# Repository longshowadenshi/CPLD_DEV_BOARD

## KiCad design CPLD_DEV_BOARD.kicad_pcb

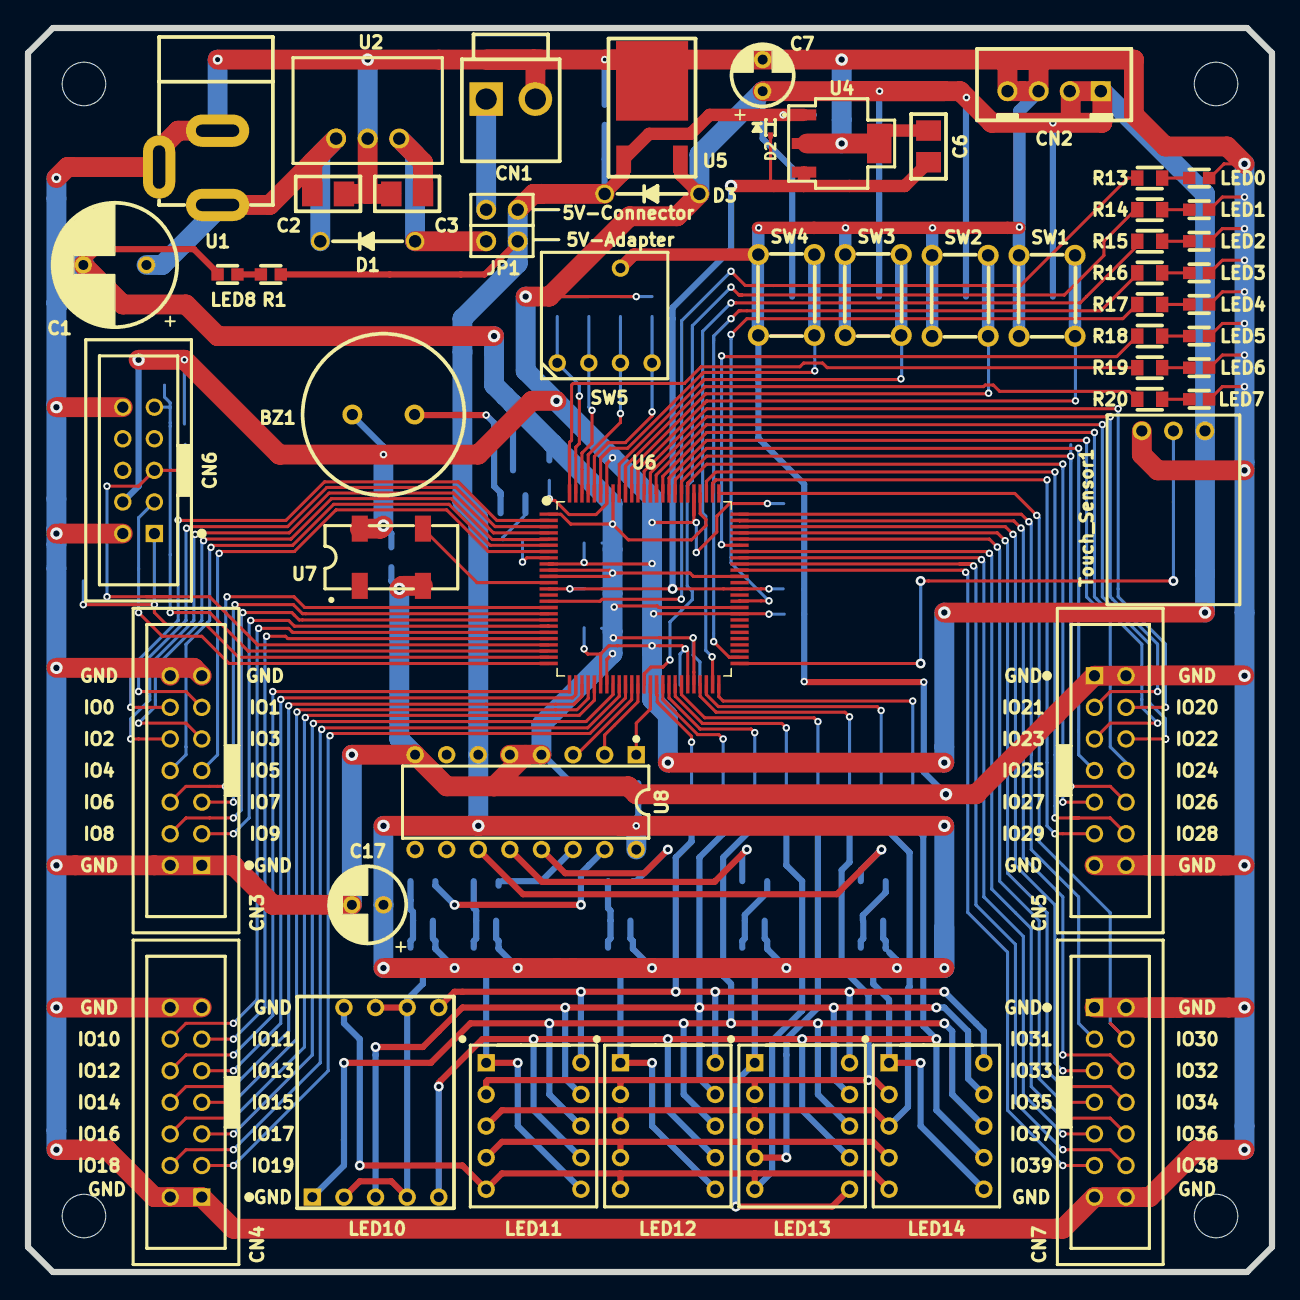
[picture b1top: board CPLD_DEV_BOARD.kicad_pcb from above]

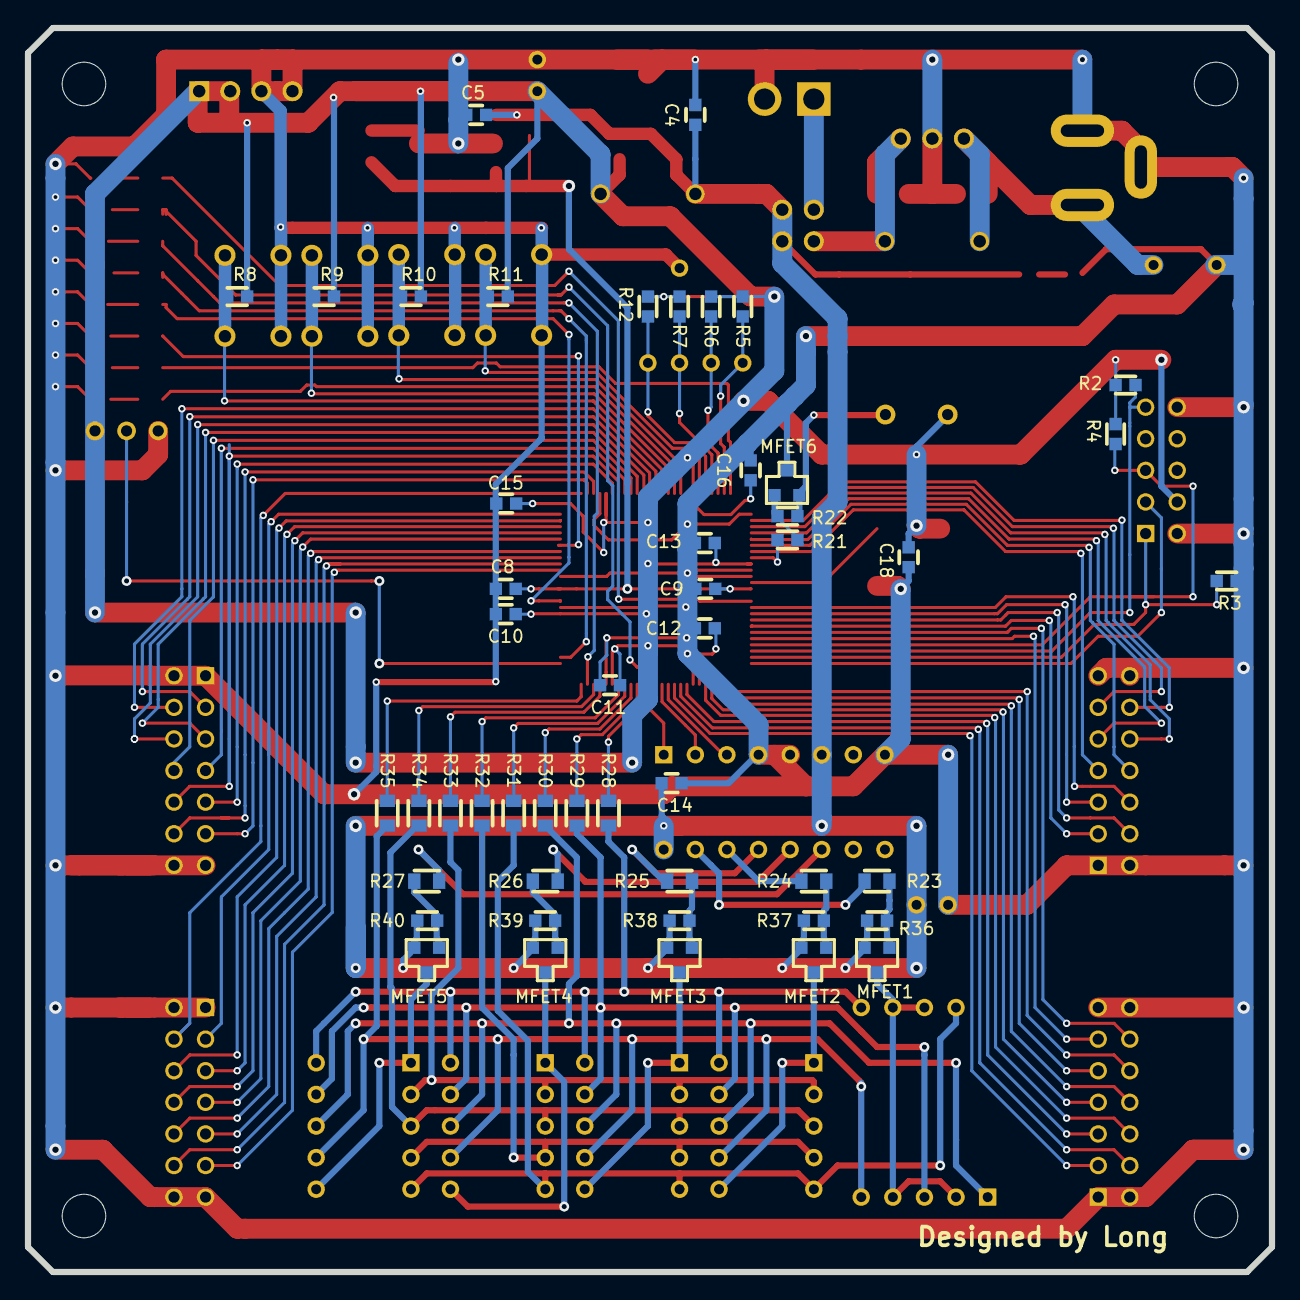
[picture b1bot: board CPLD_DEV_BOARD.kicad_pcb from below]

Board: 2 copper layers, 100.0 x 100.0 mm, 103 parts (49 on the bottom side), 115 nets.

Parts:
BZ1: Buzzer; BUZ_5_12.6
C1: 470uf/25V; 470uF-25V
C2, C3, C6: 10uF; C_3216
C4, C8, C9, C10, C11, C12, C13, C14, C15, C16, C18: 0.1uF; C0603C104Z3VACTU
C5: 1uF; C0603C104Z3VACTU
C7: 22uf/16V; 10uF-16v
C17: 220uF/16V; 220uF-16V
CN1: B2B-VH; cn_B2P-VH
CN2: B4B-XH-A; cn_B4B-XH-A
CN3, CN4, CN5, CN7: 14PIN; HIF3FC-14PA
CN6: HIF3FC-10A-2.54DSA; HIF3FC-10PA
D1, D3: 1DS4
D2: RB521S30T1G
JP1: jumper
LED0, LED1, LED2, LED3, LED4, LED5, LED6, LED7: BLUE; C1608C0G1H682J
LED8: GREEN; C1608C0G1H682J
LED10: LED__HDSP_5507; HDSP5307
LED11, LED12, LED13, LED14: SA39-12SRWA; SA39-129RWB
MFET1, MFET2, MFET3, MFET4, MFET5, MFET6: SSM3J334R
R1: 470; C1608C0G1H682J
R2, R3, R4: 4.7k; C1608C0G1H682J
R5, R6, R7, R8, R9, R10, R11, R12, R21, R22, R36, R37, R38, R39, R40: 10k; C1608C0G1H682J
R13, R14, R15, R16, R17, R18, R19, R20, R23, R24, R25, R26, R27, R28, R29, R30, R31, R32, R33, R34, R35: 1k; C_1220
SW1, SW2, SW3, SW4: SKHHBY
SW5: SW_Coded; S-2030A
Touch_Sensor1: 3PIN; Touch_Sensor
U1: MJ-179P; MJ179P
U2: R-78E5.0-0.5
U4: MCP1826S
U5: NJM2391DL1-33
U6: 5M80ZT100C5N
U7: SG636PCE8M
U8: 74HCT138; 74HC161AP

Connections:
+1V8: C6.1, C8.1, C9.1, D2.1, U4.3, U6.13, U6.63
+3V3: BZ1.1, C7.1, C10.1, C11.1, C12.1, C13.1, C15.1, C16.1, C18.1, CN2.1, CN2.2, CN6.4, D3.1, R2.1, R4.1, R5.1, R6.1, R7.1, R8.1, R9.1, R10.1, R11.1, R12.1, Touch_Sensor1.1, U5.3, U6.9, U6.31, U6.45, U6.59, U6.80, U6.94, U7.4
+5V: C4.1, C5.1, C14.1, C17.1, D2.2, D3.2, JP1.2, JP1.4, MFET1.2, MFET2.2, MFET3.2, MFET4.2, MFET5.2, R1.1, R36.2, R37.2, R38.2, R39.2, R40.2, U4.1, U5.1, U8.6, U8.16
/5M80ZT100C5N/Buzzer: R21.2, U6.8
/5M80ZT100C5N/COL0: U6.39, U8.1
/5M80ZT100C5N/COL1: U6.37, U8.2
/5M80ZT100C5N/COL2: U6.36, U8.3
/5M80ZT100C5N/IO0: CN3.12, U6.2
/5M80ZT100C5N/IO1: CN3.11, U6.3
/5M80ZT100C5N/IO2: CN3.10, U6.4
/5M80ZT100C5N/IO3: CN3.9, U6.5
/5M80ZT100C5N/IO4: CN3.8, U6.6
/5M80ZT100C5N/IO5: CN3.7, U6.7
/5M80ZT100C5N/IO6: CN3.6, U6.16
/5M80ZT100C5N/IO7: CN3.5, U6.17
/5M80ZT100C5N/IO8: CN3.4, U6.18
/5M80ZT100C5N/IO9: CN3.3, U6.19
/5M80ZT100C5N/IO10: CN4.12, U6.20
/5M80ZT100C5N/IO11: CN4.11, U6.21
/5M80ZT100C5N/IO12: CN4.10, U6.26
/5M80ZT100C5N/IO13: CN4.9, U6.27
/5M80ZT100C5N/IO14: CN4.8, U6.28
/5M80ZT100C5N/IO15: CN4.7, U6.29
/5M80ZT100C5N/IO16: CN4.6, U6.30
/5M80ZT100C5N/IO17: CN4.5, U6.33
/5M80ZT100C5N/IO18: CN4.4, U6.34
/5M80ZT100C5N/IO19: CN4.3, U6.35
/5M80ZT100C5N/IO20: CN5.4, U6.88
/5M80ZT100C5N/IO21: CN5.3, U6.87
/5M80ZT100C5N/IO22: CN5.6, U6.86
/5M80ZT100C5N/IO23: CN5.5, U6.85
/5M80ZT100C5N/IO24: CN5.8, U6.84
/5M80ZT100C5N/IO25: CN5.7, U6.83
/5M80ZT100C5N/IO26: CN5.10, U6.82
/5M80ZT100C5N/IO27: CN5.9, U6.81
/5M80ZT100C5N/IO28: CN5.12, U6.78
/5M80ZT100C5N/IO29: CN5.11, U6.77
/5M80ZT100C5N/IO30: CN7.4, U6.76
/5M80ZT100C5N/IO31: CN7.3, U6.75
/5M80ZT100C5N/IO32: CN7.6, U6.74
/5M80ZT100C5N/IO33: CN7.5, U6.73
/5M80ZT100C5N/IO34: CN7.8, U6.72
/5M80ZT100C5N/IO35: CN7.7, U6.71
/5M80ZT100C5N/IO36: CN7.10, U6.69
/5M80ZT100C5N/IO37: CN7.9, U6.68
/5M80ZT100C5N/IO38: CN7.12, U6.67
/5M80ZT100C5N/IO39: CN7.11, U6.66
/5M80ZT100C5N/LED0: R13.1, U6.15
/5M80ZT100C5N/LED1: R14.1, U6.38
/5M80ZT100C5N/LED2: R15.1, U6.49
/5M80ZT100C5N/LED3: R16.1, U6.52
/5M80ZT100C5N/LED4: R17.1, U6.61
/5M80ZT100C5N/LED5: R18.1, U6.70
/5M80ZT100C5N/LED6: R19.1, U6.100
/5M80ZT100C5N/LED7: R20.1, U6.91
/5M80ZT100C5N/PB0: R8.2, SW1.3, SW1.4, U6.89
/5M80ZT100C5N/PB1: R9.2, SW2.3, SW2.4, U6.90
/5M80ZT100C5N/PB2: R10.2, SW3.3, SW3.4, U6.92
/5M80ZT100C5N/PB3: R11.2, SW4.3, SW4.4, U6.95
/5M80ZT100C5N/ROW0: R28.2, U6.40
/5M80ZT100C5N/ROW1: R29.2, U6.41
/5M80ZT100C5N/ROW2: R30.2, U6.42
/5M80ZT100C5N/ROW3: R31.2, U6.43
/5M80ZT100C5N/ROW4: R32.2, U6.44
/5M80ZT100C5N/ROW5: R33.2, U6.47
/5M80ZT100C5N/ROW6: R34.2, U6.48
/5M80ZT100C5N/ROW7: R35.2, U6.50
/5M80ZT100C5N/SW_CODED_1: R12.2, SW5.1, U6.96
/5M80ZT100C5N/SW_CODED_2: R7.2, SW5.2, U6.97
/5M80ZT100C5N/SW_CODED_4: R6.2, SW5.4, U6.98
/5M80ZT100C5N/SW_CODED_8: R5.2, SW5.8, U6.99
/5M80ZT100C5N/TCK: CN6.1, R3.1, U6.24
/5M80ZT100C5N/TDI: CN6.9, R2.2, U6.23
/5M80ZT100C5N/TDO: CN6.3, U6.25
/5M80ZT100C5N/TMS: CN6.5, R4.2, U6.22
/5M80ZT100C5N/Touch_Sensor: Touch_Sensor1.2, U6.51
GND: C1.2, C2.2, C3.2, C4.2, C5.2, C6.2, C7.2, C8.2, C9.2, C10.2, C11.2, C12.2, C13.2, C14.2, C15.2, C16.2, C17.2, C18.2, CN1.2, CN2.3, CN2.4, CN3.1, CN3.2, CN3.13, CN3.14, CN4.1, CN4.2, CN4.13, CN4.14, CN5.1, CN5.2, CN5.13, CN5.14, CN6.2, CN6.10, CN7.1, CN7.2, CN7.13, CN7.14, LED0.2, LED1.2, LED2.2, LED3.2, LED4.2, LED5.2, LED6.2, LED7.2, LED8.2, MFET6.3, R3.2, SW1.1, SW1.2, SW2.1, SW2.2, SW3.1, SW3.2, SW4.1, SW4.2, SW5.C, Touch_Sensor1.3, U1.2, U1.3, U2.2, U4.2, U4.4, U5.2, U6.1, U6.10, U6.11, U6.32, U6.46, U6.60, U6.65, U6.79, U6.93, U7.2, U8.4, U8.5, U8.8
unnamed: BZ1.2, MFET6.2, R22.1
unnamed: C1.1, C2.1, D1.2, U1.1, U2.1
unnamed: C3.1, D1.1, JP1.3, U2.3
unnamed: CN1.1, JP1.1
unnamed: LED0.1, R13.2
unnamed: LED1.1, R14.2
unnamed: LED2.1, R15.2
unnamed: LED3.1, R16.2
unnamed: LED4.1, R17.2
unnamed: LED5.1, R18.2
unnamed: LED6.1, R19.2
unnamed: LED7.1, R20.2
unnamed: LED8.1, R1.2
unnamed: LED10.1, LED11.8, LED12.8, LED13.8, LED14.8, R30.1
unnamed: LED10.2, LED10.4, LED10.7, LED10.8, MFET1.3
unnamed: LED10.3, LED11.9, LED12.9, LED13.9, LED14.9, R29.1
unnamed: LED10.5, LED11.7, LED12.7, LED13.7, LED14.7, R35.1
unnamed: LED10.6, LED11.10, LED12.10, LED13.10, LED14.10, R28.1
unnamed: LED10.9, LED11.5, LED12.5, LED13.5, LED14.5, R31.1
unnamed: LED11.1, LED11.6, MFET2.3
unnamed: LED11.2, LED12.2, LED13.2, LED14.2, R33.1
unnamed: LED11.3, LED12.3, LED13.3, LED14.3, R34.1
unnamed: LED11.4, LED12.4, LED13.4, LED14.4, R32.1
unnamed: LED12.1, LED12.6, MFET3.3
unnamed: LED13.1, LED13.6, MFET4.3
unnamed: LED14.1, LED14.6, MFET5.3
unnamed: MFET1.1, R23.1, R36.1
unnamed: MFET2.1, R24.1, R37.1
unnamed: MFET3.1, R25.1, R38.1
unnamed: MFET4.1, R26.1, R39.1
unnamed: MFET5.1, R27.1, R40.1
unnamed: MFET6.1, R21.1, R22.2
unnamed: R23.2, U8.15
unnamed: R24.2, U8.14
unnamed: R25.2, U8.13
unnamed: R26.2, U8.12
unnamed: R27.2, U8.11
unnamed: U6.12, U7.3
